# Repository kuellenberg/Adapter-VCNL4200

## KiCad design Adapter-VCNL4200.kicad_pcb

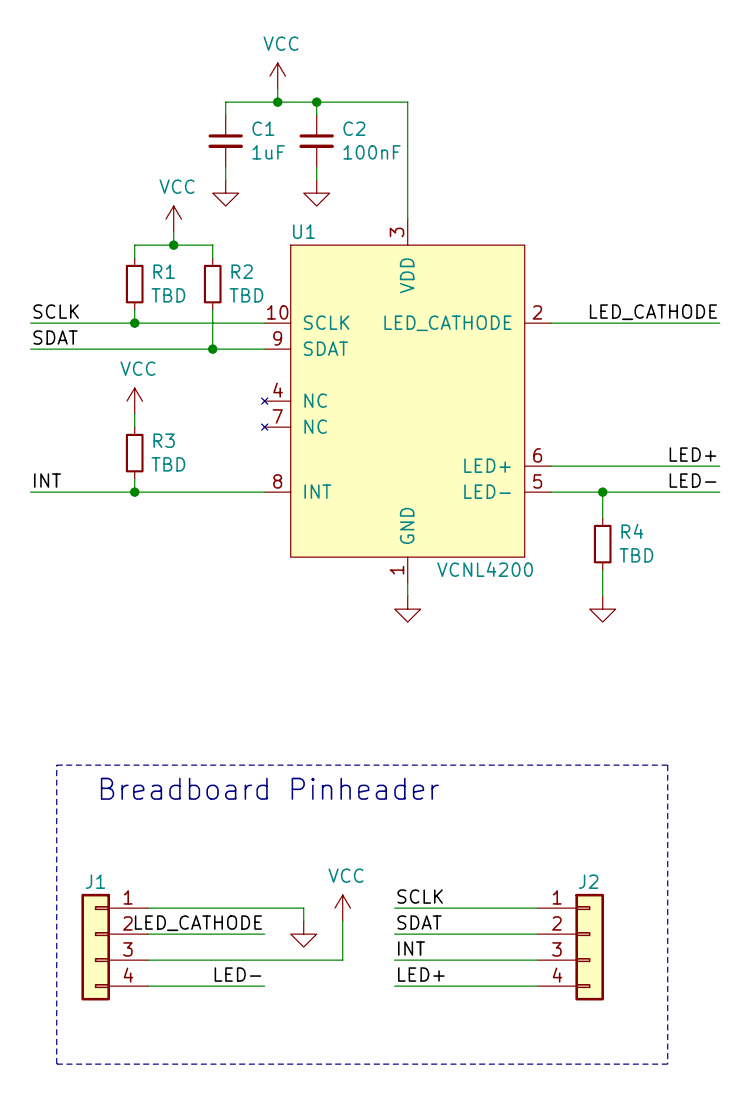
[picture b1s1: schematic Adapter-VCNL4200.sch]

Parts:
C1: 1uF; C_0805_2012Metric_Pad1.18x1.45mm_HandSolder
C2: 100nF; C_0805_2012Metric_Pad1.18x1.45mm_HandSolder
J1, J2: Conn_01x04; PinHeader_1x04_P2.54mm_Vertical
R1, R2, R3, R4: TBD; R_0805_2012Metric_Pad1.20x1.40mm_HandSolder
U1: VCNL4200; VCNL4200_HS

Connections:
/INT: J2.3, R3.2, U1.8 (INT)
/LED+: J2.4, U1.6 (LED+)
/LED-: J1.4, R4.1, U1.5 (LED-)
/LED_CATHODE: J1.2, U1.2 (LED_CATHODE)
/SCLK: J2.1, R1.2, U1.10 (SCLK)
/SDAT: J2.2, R2.2, U1.9 (SDAT)
GND: C1.2, C2.2, J1.1, R4.2, U1.1 (GND)
VCC: C1.1, C2.1, J1.3, R1.1, R2.1, R3.1, U1.3 (VDD)

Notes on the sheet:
Breadboard Pinheader

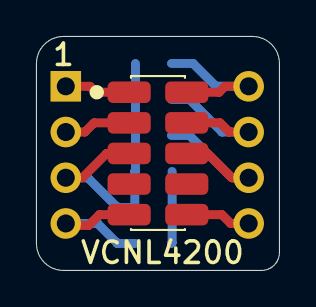
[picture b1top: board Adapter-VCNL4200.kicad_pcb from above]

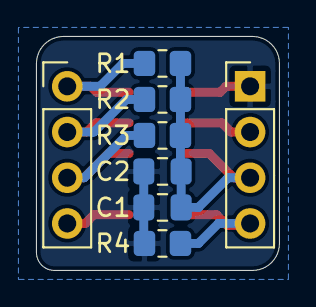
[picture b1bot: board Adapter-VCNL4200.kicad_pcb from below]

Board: 2 copper layers, 13.5 x 13.0 mm, 9 parts (8 on the bottom side), 8 nets.

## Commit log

2021-11-22 Created gerbers
